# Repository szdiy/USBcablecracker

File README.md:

USBcablecracker
============
USB Cable Cracker is a device that measures the resistance of USB cable.
It measures the serial resistance of VCC + GND or D+ or D-.
And if you are not satisfy with the resistance, you can crack the cable by yourself.
It is a Arduino Leonardo compatible board, with some extend pins.

Schematic
------------
[PDF][schem]

BOM
------------
[CSV][bom]

PCB
------------

Photo
------------

License
------------
This project is released under the CC BY-SA license.

Support
------------
r@szdiy.org

Where to buy
------------

[schem]:https://github.com/szdiy/USBcablecracker/raw/master/hardware/USBcablecracker.pdf
[bom]:https://github.com/szdiy/USBcablecracker/raw/master/hardware/manufature/USBcablecracker_bom.csv

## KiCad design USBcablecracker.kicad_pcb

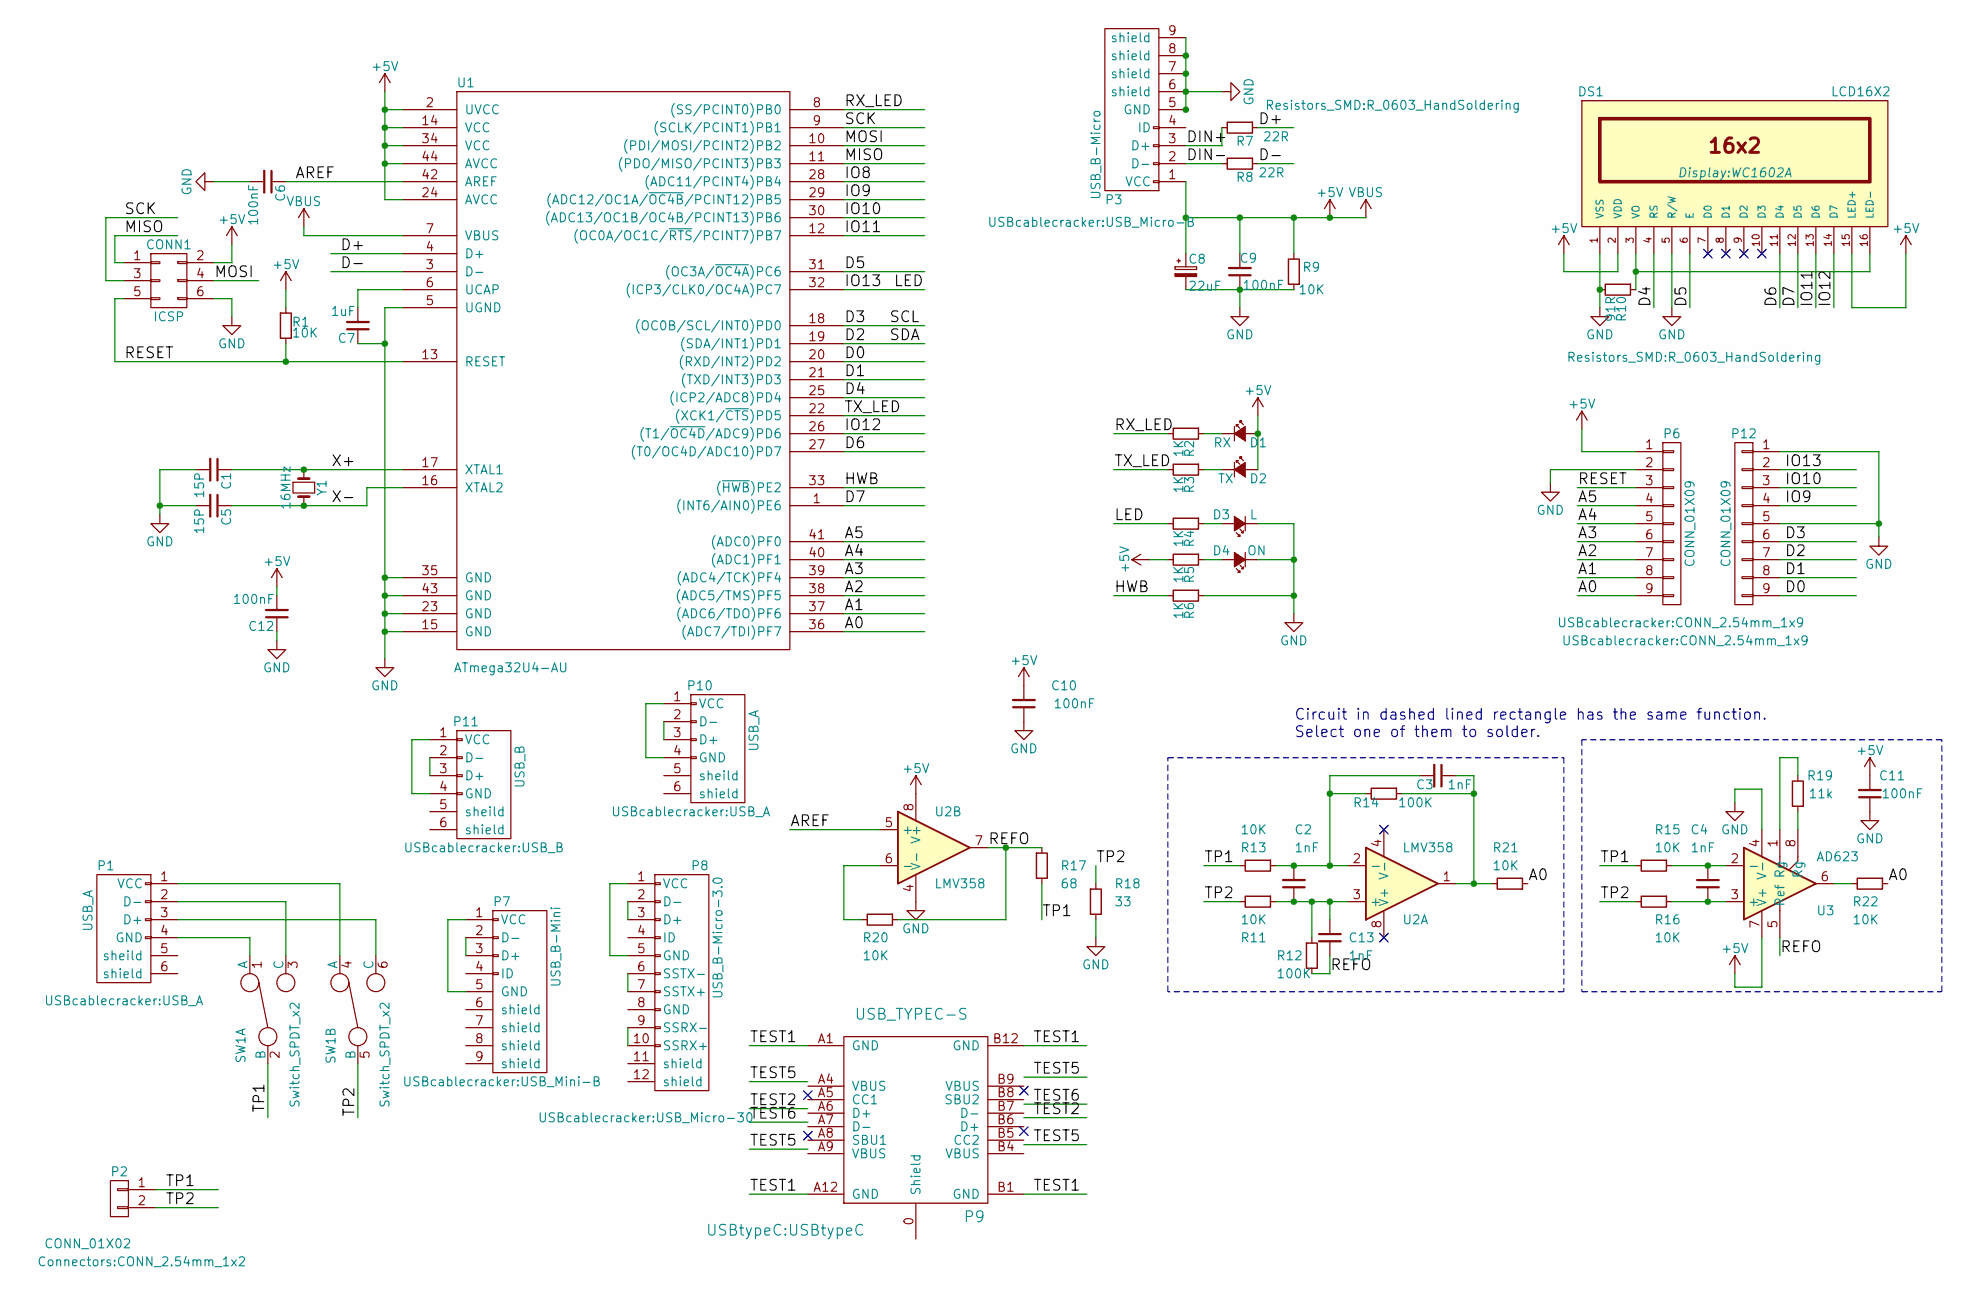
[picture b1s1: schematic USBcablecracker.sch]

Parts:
C1, C5: 15P; C_0603_HandSoldering
C2, C3, C4, C13: 1nF; C_0603_HandSoldering
C6, C9, C10, C11, C12: 100nF; C_0603_HandSoldering
C7: 1uF; C_0603_HandSoldering
C8: 22uF; Tantalum_Case-A_EIA-3216-18_Wave
CONN1: ICSP; CONN_2.54mm_2x3
D1: RX; LED_0603
D2: TX; LED_0603
D3: L; LED_0603
D4: ON; LED_0603
DS1: LCD16X2; WC1602A
P1, P10: USB_A
P2: CONN_01X02; CONN_2.54mm_1x2
P3: USB_B-Micro; USB_Micro-B
P6, P12: CONN_01X09; CONN_2.54mm_1x9
P7: USB_B-Mini; USB_Mini-B
P8: USB_B-Micro-3.0; USB_Micro-30
P9: USB_TYPEC-S; USBtypeC
P11: USB_B
R1, R9, R11, R13, R15, R16, R20, R21, R22: 10K; R_0603_HandSoldering
R2, R3, R4, R5, R6: 1K; R_0603_HandSoldering
R7, R8: 22R; R_0603_HandSoldering
R10: 91R; R_0603_HandSoldering
R12, R14: 100K; R_0603_HandSoldering
R17: 68; R_0603_HandSoldering
R18: 33; R_0603_HandSoldering
R19: 11k; R_0603_HandSoldering
SW1: Switch_SPDT_x2; DPDT
U1: ATmega32U4-AU; TQFP-44_10x10mm_Pitch0.8mm
U2: LMV358; SOIC-8_3.9x4.9mm_Pitch1.27mm
U3: AD623; SOIC-8_3.9x4.9mm_Pitch1.27mm
Y1: 16MHz; crystal_FA238-TSX3225

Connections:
+5C: C8.1, C9.2, C10.2, C11.2, C12.2, CONN1.2, D1.2 (A), D2.2 (A), DS1.2 (VDD), DS1.15 (LED+), P3.1 (VCC), P6.1, R1.1, R5.2, R9.2, U1.2 (UVCC), U1.7 (VBUS), U1.14 (VCC), U1.24 (AVCC), U1.34 (VCC), U1.44 (AVCC), U2.8 (V+), U3.7 (V+)
/A0: P6.9, R21.1, R22.1, U1.36 ((ADC7/TDI)PF7)
/A1: P6.8, U1.37 ((ADC6/TDO)PF6)
/A2: P6.7, U1.38 ((ADC5/TMS)PF5)
/A3: P6.6, U1.39 ((ADC4/TCK)PF4)
/A4: P6.5, U1.40 ((ADC1)PF1)
/A5: P6.4, U1.41 ((ADC0)PF0)
/AREF: C6.1, U1.42 (AREF), U2.5 (+)
/D0: P12.9, U1.20 ((RXD/INT2)PD2)
/D1: P12.8, U1.21 ((TXD/INT3)PD3)
/D2: P12.7, U1.19 ((SDA/INT1)PD1)
/D3: P12.6, U1.18 ((OC0B/SCL/INT0)PD0)
/D4: DS1.4 (RS), U1.25 ((ICP2/ADC8)PD4)
/D5: DS1.6 (E), U1.31 ((OC3A/~OC4A~)PC6)
/D6: DS1.11 (D4), U1.27 ((T0/OC4D/ADC10)PD7)
/D7: DS1.12 (D5), U1.1 ((INT6/AIN0)PE6)
/D+: R7.1, U1.4 (D+)
/D-: R8.1, U1.3 (D-)
/DIN+: P3.3 (D+), R7.2
/DIN-: P3.2 (D-), R8.2
/HWB: R6.2, U1.33 ((~HWB~)PE2)
/IO8: U1.28 ((ADC11/PCINT4)PB4)
/IO9: P12.4, U1.29 ((ADC12/OC1A/~OC4B~/PCINT12)PB5)
/IO10: P12.3, U1.30 ((ADC13/OC1B/OC4B/PCINT13)PB6)
/IO11: DS1.13 (D6), U1.12 ((OC0A/OC1C/~RTS~/PCINT7)PB7)
/IO12: DS1.14 (D7), U1.26 ((T1/~OC4D~/ADC9)PD6)
/IO13: P12.2, R4.2, U1.32 ((ICP3/CLK0/OC4A)PC7)
/MISO: CONN1.1, U1.11 ((PDO/MISO/PCINT3)PB3)
/MOSI: CONN1.4, U1.10 ((PDI/MOSI/PCINT2)PB2)
/REFO: C13.2, R12.2, R17.1, R20.1, U2.7, U3.5 (Ref)
/RESET: CONN1.5, P6.3, R1.2, U1.13 (RESET)
/RX_LED: R2.2, U1.8 ((SS/PCINT0)PB0)
/SCK: CONN1.3, U1.9 ((SCLK/PCINT1)PB1)
/TEST1: P9.A1 (GND), P9.A12 (GND), P9.B1 (GND), P9.B12 (GND)
/TEST2: P9.A6 (D+), P9.B6 (D+)
/TEST5: P9.A4 (VBUS), P9.A9 (VBUS), P9.B4 (VBUS), P9.B9 (VBUS)
/TEST6: P9.A7 (D-), P9.B7 (D-)
/TP1: P2.1, R13.2, R15.2, R17.2, SW1.2 (B)
/TP2: P2.2, R11.2, R16.2, R18.1, SW1.5 (B)
/TX_LED: R3.2, U1.22 ((XCK1/~CTS~)PD5)
/X+: C1.1, U1.17 (XTAL1), Y1.1
/X-: C5.1, U1.16 (XTAL2), Y1.2
GND: C1.2, C5.2, C6.2, C7.1, C8.2, C9.1, C10.1, C11.1, C12.1, CONN1.6, D3.1 (K), D4.1 (K), DS1.1 (VSS), DS1.5 (R/W), P3.5 (GND), P3.6 (shield), P3.7 (shield), P3.8 (shield), P3.9 (shield), P6.2, P12.1, P12.5, R6.1, R9.1, R10.2, R18.2, U1.5 (UGND), U1.15 (GND), U1.23 (GND), U1.35 (GND), U1.43 (GND), U2.4 (V-), U3.4 (V-)
unnamed: C2.2, C3.2, R13.1, R14.2, U2.2 (-)
unnamed: C3.1, R14.1, R21.2, U2.1
unnamed: C4.1, R15.1, U3.2 (-)
unnamed: C4.2, R16.1, U3.3 (+)
unnamed: C7.2, U1.6 (UCAP)
unnamed: C2.1, C13.1, R11.1, R12.1, U2.3 (+)
unnamed: D1.1 (K), R2.1
unnamed: D2.1 (K), R3.1
unnamed: D3.2 (A), R4.1
unnamed: D4.2 (A), R5.1
unnamed: DS1.3 (VO), DS1.16 (LED-), R10.1
unnamed: P1.1 (VCC), SW1.4 (A)
unnamed: P1.2 (D-), SW1.3 (C)
unnamed: P1.3 (D+), SW1.6 (C)
unnamed: P1.4 (GND), SW1.1 (A)
unnamed: P7.1 (VCC), P7.5 (GND)
unnamed: P7.2 (D-), P7.3 (D+)
unnamed: P8.1 (VCC), P8.5 (GND)
unnamed: P8.2 (D-), P8.3 (D+)
unnamed: P8.6 (SSTX-), P8.7 (SSTX+)
unnamed: P8.9 (SSRX-), P8.10 (SSRX+)
unnamed: P10.1 (VCC), P10.4 (GND)
unnamed: P10.2 (D-), P10.3 (D+)
unnamed: P11.1 (VCC), P11.4 (GND)
unnamed: P11.2 (D-), P11.3 (D+)
unnamed: R19.1, U3.8 (Rg)
unnamed: R19.2, U3.1 (Rg)
unnamed: R20.2, U2.6 (-)
unnamed: R22.2, U3.6

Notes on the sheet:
Circuit in dashed lined rectangle has the same function. Select one of them to solder.

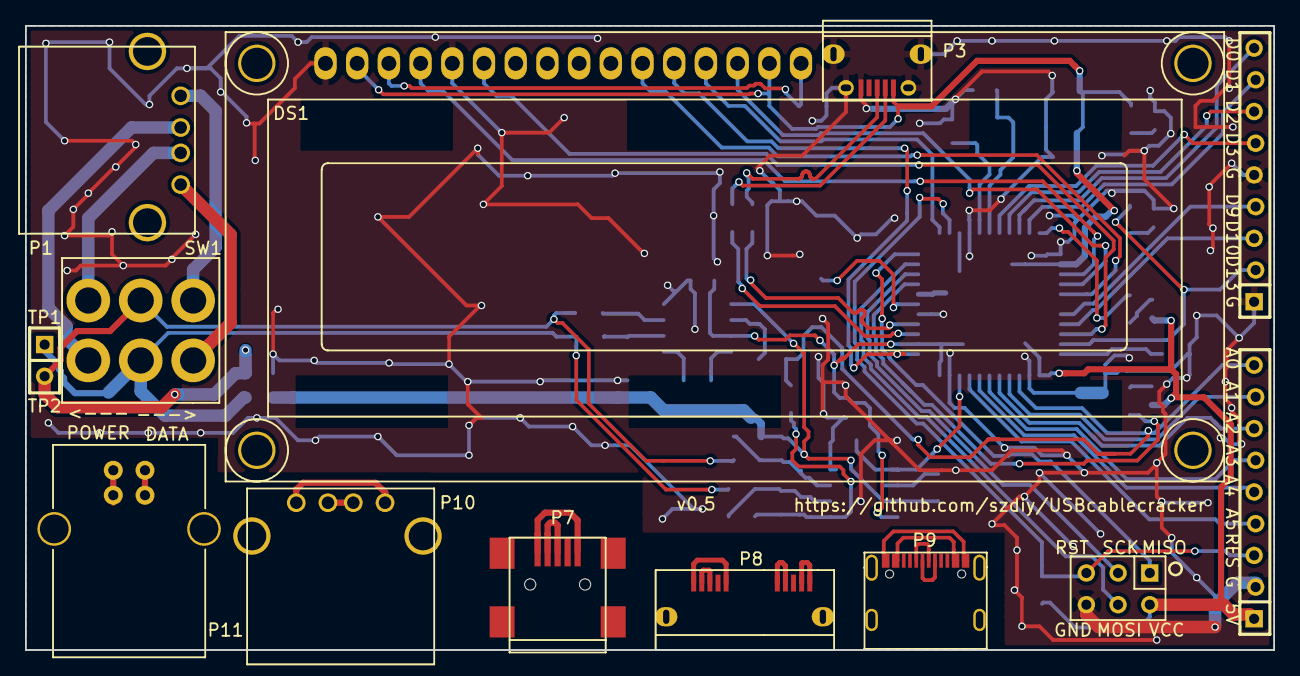
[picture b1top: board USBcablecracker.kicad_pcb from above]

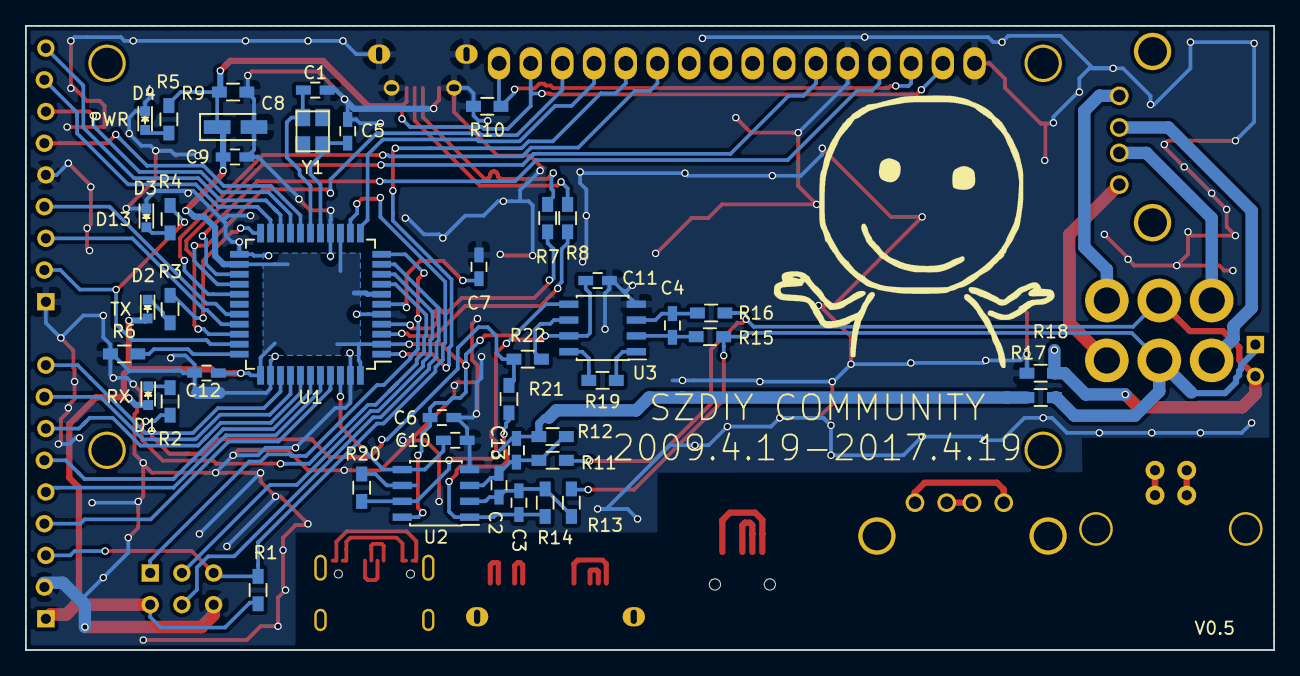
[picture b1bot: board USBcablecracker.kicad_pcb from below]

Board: 2 copper layers, 100.0 x 50.0 mm, 56 parts (43 on the bottom side), 71 nets.

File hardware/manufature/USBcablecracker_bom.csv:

Comment,Designator,Footprint
100nF/10V,"C6,C9,C10,C11,C12",C_0603
33R/1%,R18,R_0603
68R/1%,R17,R_0603
15PF,"C1,C5",C_0603
1nF,"C2,C3,C4,C13",C_0603
1uF,C7,C_0603
LED_Yellow,D1,LED_0603
TX_Green,D2,LED_0603
LED_Blue,D3,LED_0603
LED_Red,D4,LED_0603
10K/1%,"R1,R9,R11,R13,R15,R16,R20,R21,R22",R_0603
1K/1%,"R2,R3,R4,R5,R6",R_0603
22R/1%,"R7,R8",R_0603
91R/1%,R10,R_0603
100K/1%,"R12,R14",R_0603
11k/1%,R19,R_0603
16MHz,Y1,crystal_FA238-TSX3225
22uF/10V,C8,Tantalum_Case-A_EIA-3216-18_Wave

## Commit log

2016-12-23 alpha version
2017-02-24 ATtiny85>>Atmega32u4
2017-02-25 update pcb
2017-02-26 check
2017-02-26 update images
2017-05-08 Version 0.4 finished. Solved UCAP inner linear regulator problem. Modified library, footprints, instrumentation amplifier common mode input voltage, modified AREF output load.
2017-05-09 fangzhou
2017-05-10 Modified two 9-pin header distance and modified all via with not net to net GND. Add gitinore file.
2017-05-10 updated gerber
2017-06-13 Add UserGuide.txt
2017-10-05 Modify image url and some typographic error.
2017-10-05 Move arduino project file to a folder with the same name
2017-10-05 Remove DS18B20 temperature sensor
